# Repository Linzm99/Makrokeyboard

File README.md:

# Makrokeyboard
Open Source Makrokeyboard based on Atmega32U4

## Code

The Code for the Makrokeyboard was written for the Arduino IDE, which supports the Atmega32U4 as Arduino Leonardo/Pro Micro. For uploading "Arduino Leonardo" or "Arduino (Pro) Micro" should be selected as Board. The COM Port selector will show the Atmega32U4 as well.
Hint: If your Chip wasn't flashed with a bootloader you have to do that first. This requires soldering a ISP Connector and flashing via (for example) Arduino ISP. [Tutorial from Leon Anavi](https://www.youtube.com/watch?v=ToMrxnRNHM4)

## Parts

Following Parts are required:

- 1x USB-C-Connector
- 2x 5k1 Resistor 0805
- 1x FSMD050R
- 1x 0R Resistor
- 21x SK6812 rear mounted addressable LED
- 20x Diodes 0805
- 20x Keyboard Switches
- 1x 16MHz Quarz
- 1x Atmega32U4 TQFP44
- 6x 100nF 1206
- 2x 1uF 1206
- 2x 22pF 1206
- 21x 10k Resistor 0603
- 3x 22R 1206

Created by [Linze99](https://www.twitch.tv/linze99)

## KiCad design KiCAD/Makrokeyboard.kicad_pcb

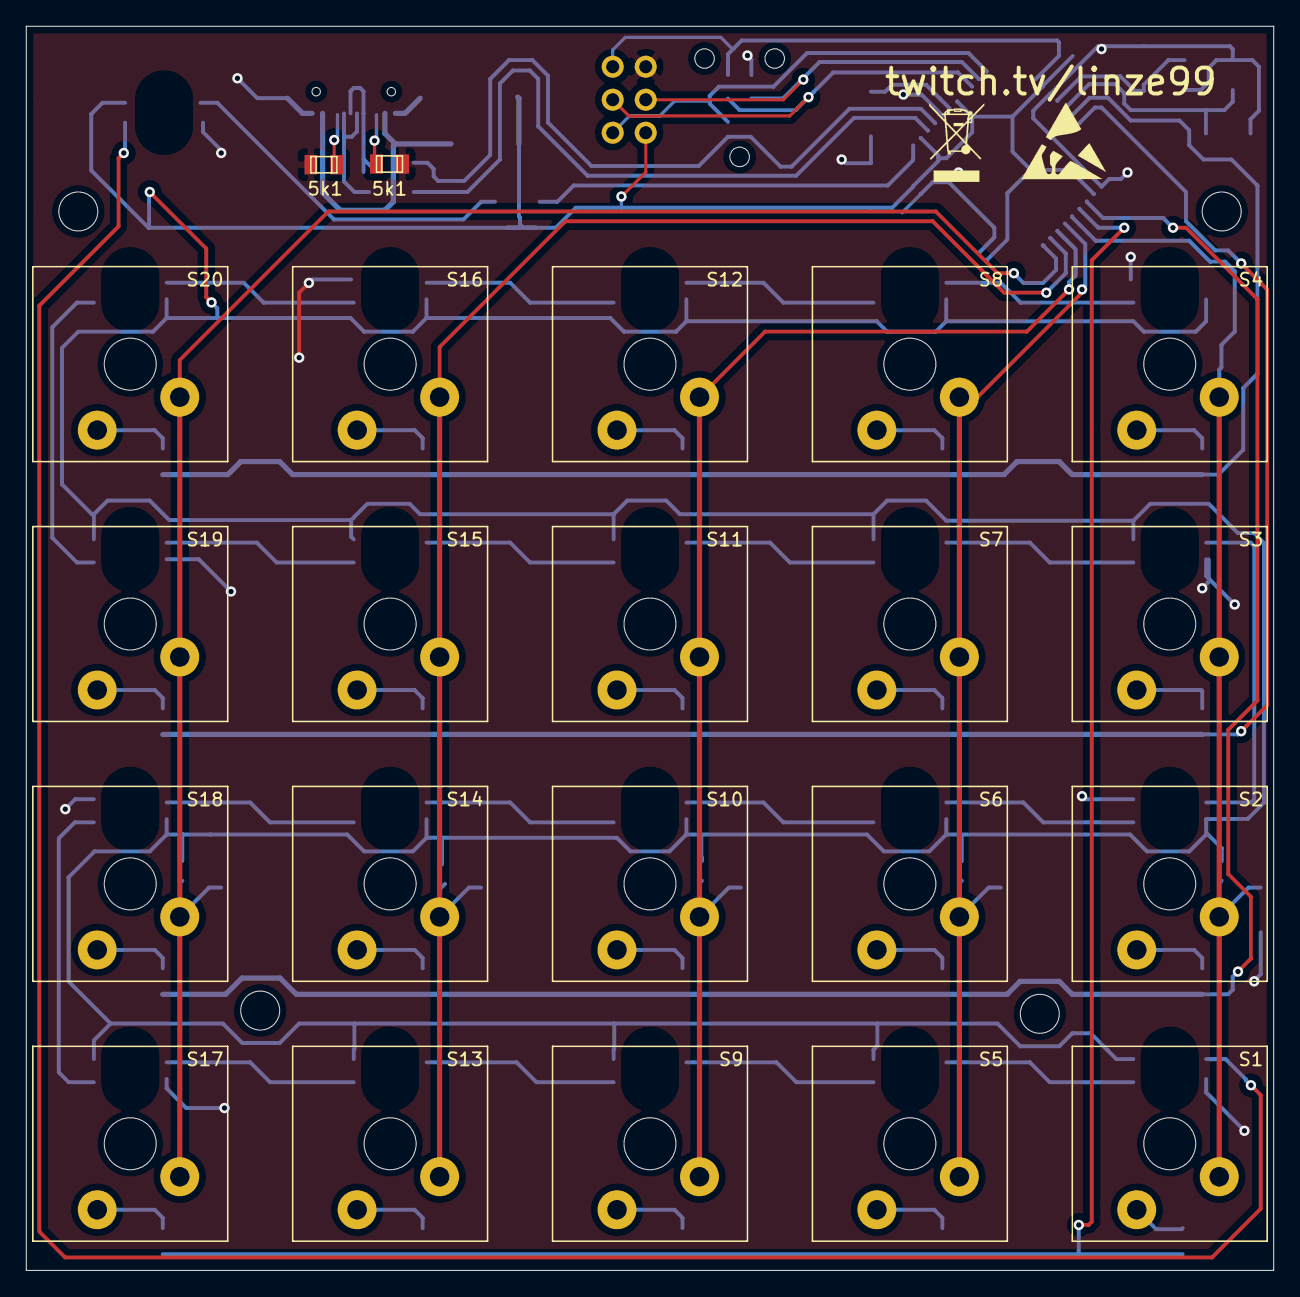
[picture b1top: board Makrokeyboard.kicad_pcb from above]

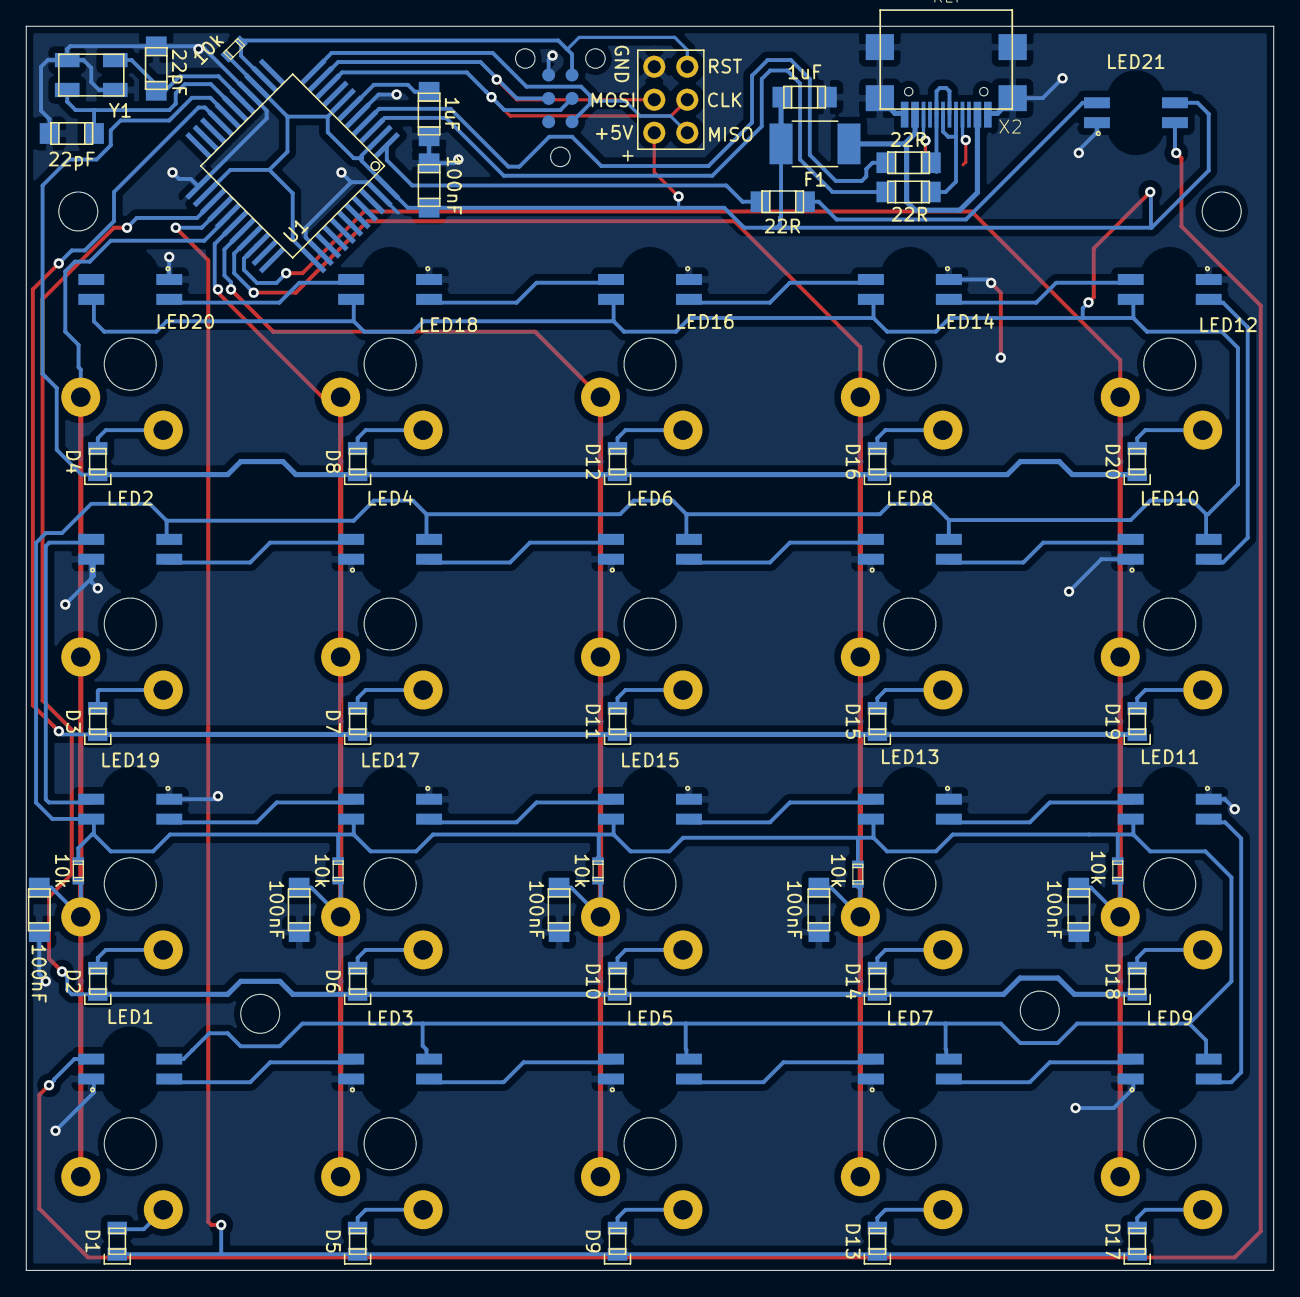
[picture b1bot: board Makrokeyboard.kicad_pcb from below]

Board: 2 copper layers, 96.0 x 95.8 mm, 92 parts (66 on the bottom side), 67 nets.

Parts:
1uF, 1uF#2: 1uF; 1206
5k1, 5k1#2: 5k1; 0805
10k, 10k#2, 10k#3, 10k#4, 10k#5, 10k#6: 10k; 0603
22R: 0R; 1206
22R#2, 22R#3: 22R; 1206
22pF, 22pF#2: 22pF; 1206
100nF, 100nF#2, 100nF#3, 100nF#4, 100nF#5, 100nF#6: 100nF; 1206
D1, D2, D3, D4, D5, D6, D7, D8, D9, D10, D11, D12, D13, D14, D15, D16, D17, D18, D19, D20: Diode; 0805d
F1: FSMD050R; 1812
LED1, LED2, LED3, LED4, LED5, LED6, LED7, LED8, LED9, LED10, LED11, LED12, LED13, LED14, LED15, LED16, LED17, LED18, LED19, LED20, LED21: ADR_LED; SK6812r
S1, S2, S3, S4, S5, S6, S7, S8, S9, S10, S11, S12, S13, S14, S15, S16, S17, S18, S19, S20: CH; CHERRYMX
U1: Atmega32U4; TQFP44
X1: Progstecker
X2: *REF; USB-TYPE-C
X3, X4, X5, X6: Mount; Mount3mm
X7: Progstecker; Progstecker_alt
Y1: 16Mhz; SMD_Crystal

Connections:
+5V: 1uF.2, 10k.1, 10k#2.1, 10k#3.1, 10k#4.1, 10k#5.1, 10k#6.2, 100nF#6.1, F1.1, LED1.1, LED2.1, LED3.1, LED4.1, LED5.1, LED6.1, LED7.1, LED8.1, LED9.1, LED10.1, LED11.1, LED12.1, LED13.1, LED14.1, LED15.1, LED16.1, LED17.1, LED18.1, LED19.1, LED20.1, LED21.1, U1.2, U1.7, U1.14, U1.24, U1.34, U1.44, X7.VDD
D+: 22R#2.1, X2.6, X2.8
D-: 22R#3.1, X2.5, X2.7
GND: 1uF.1, 1uF#2.2, 5k1.2, 5k1#2.2, 22pF.2, 22pF#2.1, 100nF.2, 100nF#2.2, 100nF#3.2, 100nF#4.2, 100nF#5.2, 100nF#6.2, LED1.3, LED2.3, LED3.3, LED4.3, LED5.3, LED6.3, LED7.3, LED8.3, LED9.3, LED10.3, LED11.3, LED12.3, LED13.3, LED14.3, LED15.3, LED16.3, LED17.3, LED18.3, LED19.3, LED20.3, LED21.3, U1.5, U1.15, U1.23, U1.35, U1.43, X1.GND, X2.0, X2.1, X2.12, X7.GND, Y1.2, Y1.4
LED: 22R.1, U1.1
unnamed: 1uF#2.1, U1.6
unnamed: 22pF#2.2, U1.16, Y1.1
unnamed: 22pF.1, U1.17, Y1.3
unnamed: D1.1, S1.2
unnamed: D2.1, S2.2
unnamed: D3.1, S3.2
unnamed: D4.1, S4.2
unnamed: D5.1, S5.2
unnamed: D6.1, S6.2
unnamed: D7.1, S7.2
unnamed: D8.1, S8.2
unnamed: D9.1, S9.2
unnamed: D10.1, S10.2
unnamed: D11.1, S11.2
unnamed: D12.1, S12.2
unnamed: D13.1, S13.2
unnamed: D14.1, S14.2
unnamed: D15.1, S15.2
unnamed: D16.1, S16.2
unnamed: D17.1, S17.2
unnamed: D18.1, S18.2
unnamed: D19.1, S19.2
unnamed: D20.1, S20.2
unnamed: F1.2, X2.2, X2.11
unnamed: LED1.2, LED21.4
unnamed: LED1.4, LED3.2
unnamed: LED2.4, LED4.2
unnamed: LED3.4, LED5.2
unnamed: LED4.4, LED6.2
unnamed: LED5.4, LED7.2
unnamed: LED6.4, LED8.2
unnamed: LED7.4, LED9.2
unnamed: LED8.4, LED10.2
unnamed: LED10.4, LED12.2
unnamed: LED9.4, LED11.2
unnamed: LED11.4, LED13.2
unnamed: LED12.4, LED14.2
unnamed: LED13.4, LED15.2
unnamed: LED14.4, LED16.2
unnamed: LED15.4, LED17.2
unnamed: LED16.4, LED18.2
unnamed: LED17.4, LED19.2
unnamed: LED18.4, LED20.2
unnamed: LED2.2, LED19.4
unnamed: 22R.2, LED21.2
unnamed: 22R#3.2, U1.3
unnamed: 22R#2.2, U1.4
unnamed: 10k#6.1, U1.13, X1.RST, X7.RST
unnamed: 5k1#2.1, X2.10
unnamed: 5k1.1, X2.4
unnamed: U1.9, X1.SCLK, X7.SCLK
unnamed: U1.10, X1.MOSI, X7.MOSI
unnamed: U1.11, X1.MISO, X7.MISO
TR1: D1.2, D5.2, D9.2, D13.2, D17.2, U1.26
TR2: D2.2, D6.2, D10.2, D14.2, D18.2, U1.25
TR3: D3.2, D7.2, D11.2, D15.2, D19.2, U1.19
TR4: D4.2, D8.2, D12.2, D16.2, D20.2, U1.18
TS1: 10k#5.2, 100nF#5.1, S1.1, S2.1, S3.1, S4.1, U1.27
TS2: 10k#4.2, 100nF#4.1, S5.1, S6.1, S7.1, S8.1, U1.28
TS3: 10k#3.2, 100nF#3.1, S9.1, S10.1, S11.1, S12.1, U1.29
TS4: 10k#2.2, 100nF#2.1, S13.1, S14.1, S15.1, S16.1, U1.30
TS5: 10k.2, 100nF.1, S17.1, S18.1, S19.1, S20.1, U1.31

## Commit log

2021-02-28 Initial Upload
2021-03-15 Slight Softwarechanges
2021-03-17 Tasten haben Defaults, letzte Taste hat Highlight
    Die Tasten haben STRG + Shift + F1 - F20 als Key
    Die zuletzt gedrückte Taste bleibt weiß
    Andere Tasten faden durch die Farben
2021-04-14 made project compiling under platformio without warnings
2021-05-06 Update Makrokeyboard.ino
    Kontrastwechsel der Farben angepasst.
2021-06-28 add hole and clamp
    add hole to fit better on switches
    add clamp to tighten keycap on switch
2022-05-21 Test for Images
2022-05-21 Added images
2022-05-21 Added Additional Info
2022-05-21 Update README.md
    Board corrected
